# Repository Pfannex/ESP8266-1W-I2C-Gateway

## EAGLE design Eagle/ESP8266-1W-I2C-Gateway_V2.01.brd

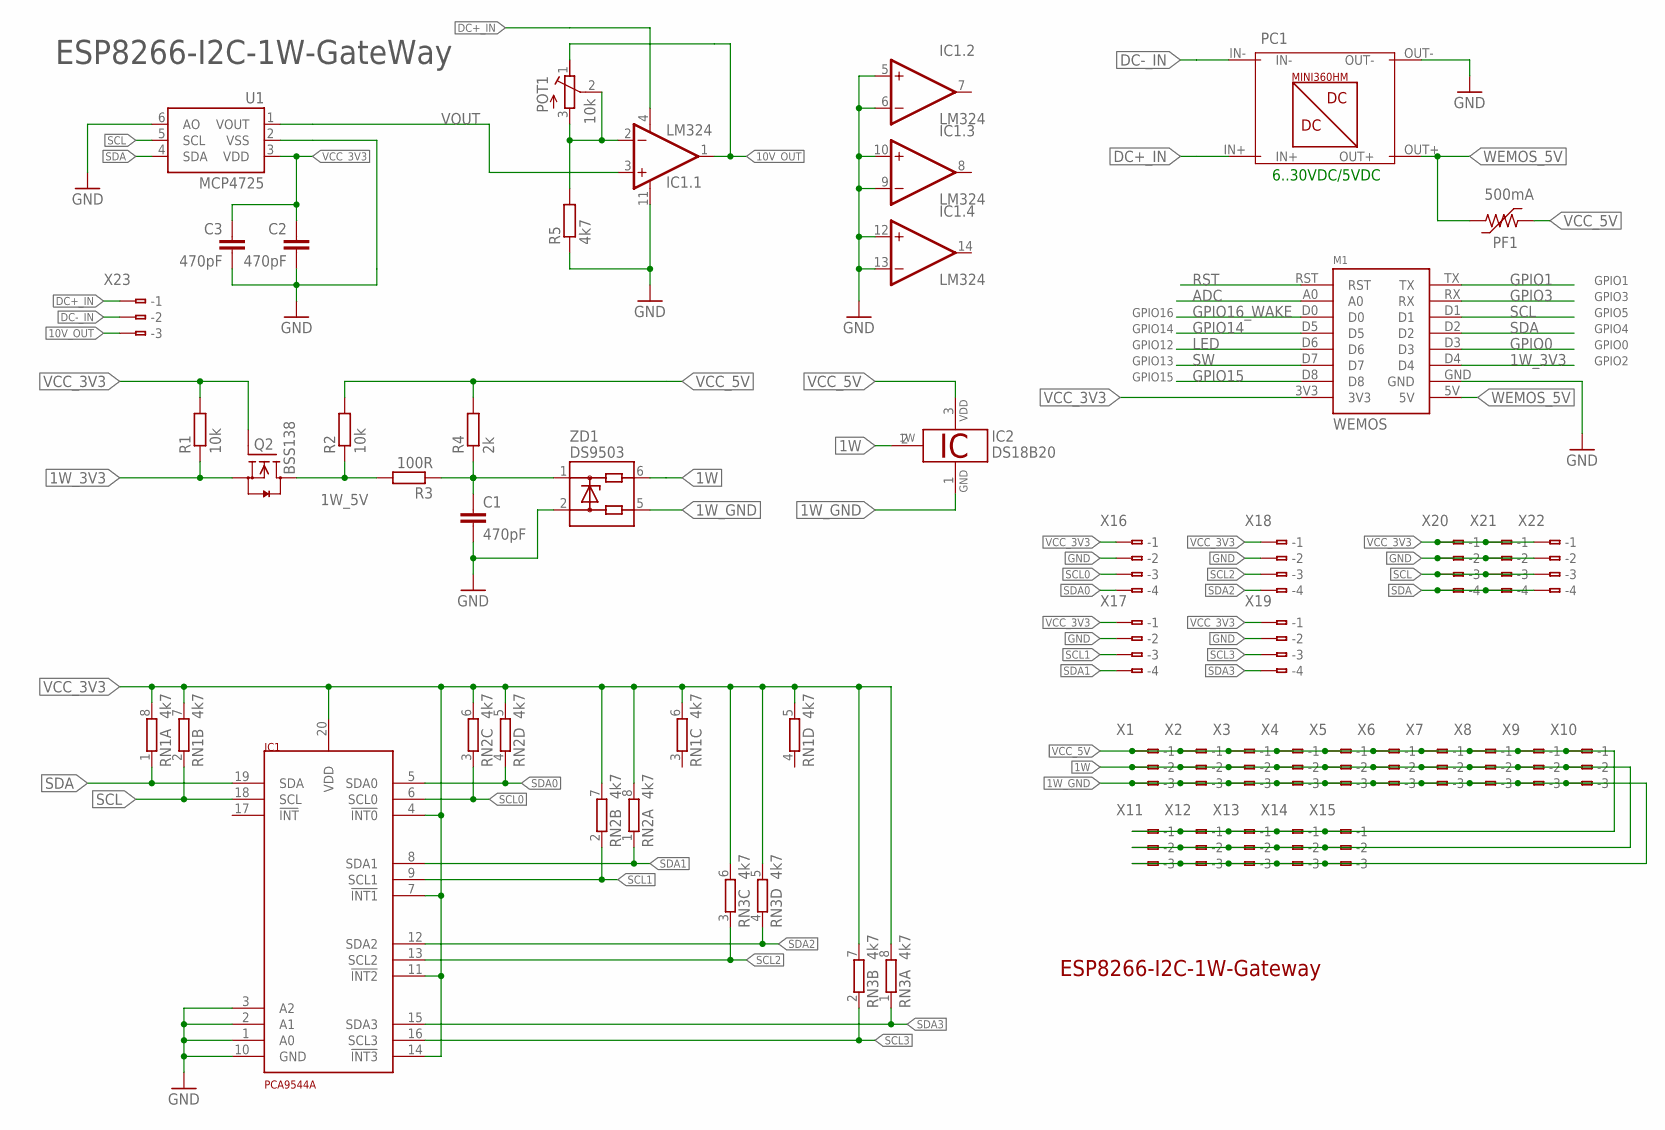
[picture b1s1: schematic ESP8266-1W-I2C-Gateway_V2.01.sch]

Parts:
C1, C2, C3: 470pF; C0805
IC1: PCA9544A; TSSOP20
IC1.: LM324; 2QSP14
IC2: DS18B20; TO92-
M1: WEMOS
PC1: MINI360HMTHROUGH-HOLE; MINI360HM
PF1: 500mA; F1206
POT1: 10k; BOURN_SMD_POTENTIOMETER
Q2: BSS138; SOT23
R1, R2: 10k; R0805
R3: 100R; R0805
R4: 2k; R0805
R5: 4k7; R0805
RN1, RN2, RN3: 4k7; 0603-ARC
U1: MCP4725; SOT23-6
X1, X2, X3, X4, X5, X6, X7, X8, X9, X10, X11, X12, X13, X14, X15, X23: MINI_3X
X16, X17, X18, X19, X20, X21, X22: MINI_4X
ZD1: DS9503; TSOC6_BYPASS_J

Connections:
1W: IC2.2 (1W), X1.B-2 (-2), X2.B-2 (-2), X3.B-2 (-2), X4.B-2 (-2), X5.B-2 (-2), X6.B-2 (-2), X7.B-2 (-2), X8.B-2 (-2), X9.B-2 (-2), X10.B-2 (-2), X11.B-2 (-2), X12.B-2 (-2), X13.B-2 (-2), X14.B-2 (-2), X15.B-2 (-2), ZD1.6
1W_3V3: M1.D4, Q2.2 (S), R1.1
1W_5V: Q2.3 (D), R2.1, R3.2
1W_GND: IC2.1 (GND), X1.B-3 (-3), X2.B-3 (-3), X3.B-3 (-3), X4.B-3 (-3), X5.B-3 (-3), X6.B-3 (-3), X7.B-3 (-3), X8.B-3 (-3), X9.B-3 (-3), X10.B-3 (-3), X11.B-3 (-3), X12.B-3 (-3), X13.B-3 (-3), X14.B-3 (-3), X15.B-3 (-3), ZD1.5
10V_OUT: IC1..1 (OUT), POT1.1 (A), X23.B-3 (-3)
ADC: M1.A0
DC+_IN: IC1..4 (V+), PC1.IN+, X23.B-1 (-1)
DC-_IN: PC1.IN-, X23.B-2 (-2)
GND: C1.2, C2.2, C3.2, IC1.1 (A0), IC1.2 (A1), IC1.3 (A2), IC1.10 (GND), IC1..5 (+IN), IC1..6 (-IN), IC1..9 (-IN), IC1..10 (+IN), IC1..11 (V-), IC1..12 (+IN), IC1..13 (-IN), M1.GND, PC1.OUT-, R5.1, U1.2 (VSS), U1.6 (AO), X16.B-2 (-2), X17.B-2 (-2), X18.B-2 (-2), X19.B-2 (-2), X20.B-2 (-2), X21.B-2 (-2), X22.B-2 (-2), ZD1.2
GPIO0: M1.D3
GPIO1: M1.TX
GPIO3: M1.RX
GPIO14: M1.D5
GPIO15: M1.D8
GPIO16_WAKE: M1.D0
LED: M1.D6
unnamed: IC1..2 (-IN), POT1.2 (S), POT1.3 (E), R5.2
unnamed: C1.1, R3.1, R4.1, ZD1.1
RST: M1.RST
SCL: IC1.18 (SCL), M1.D1, RN1.2 (1), U1.5 (SCL), X20.B-3 (-3), X21.B-3 (-3), X22.B-3 (-3)
SCL0: IC1.6 (SCL0), RN2.3 (1), X16.B-3 (-3)
SCL1: IC1.9 (SCL1), RN2.2 (1), X17.B-3 (-3)
SCL2: IC1.13 (SCL2), RN3.3 (1), X18.B-3 (-3)
SCL3: IC1.16 (SCL3), RN3.2 (1), X19.B-3 (-3)
SDA: IC1.19 (SDA), M1.D2, RN1.1, U1.4 (SDA), X20.B-4 (-4), X21.B-4 (-4), X22.B-4 (-4)
SDA0: IC1.5 (SDA0), RN2.4 (1), X16.B-4 (-4)
SDA1: IC1.8 (SDA1), RN2.1, X17.B-4 (-4)
SDA2: IC1.12 (SDA2), RN3.4 (1), X18.B-4 (-4)
SDA3: IC1.15 (SDA3), RN3.1, X19.B-4 (-4)
SW: M1.D7
VCC_3V3: C2.1, C3.1, IC1.4 (!INT0), IC1.7 (!INT1), IC1.11 (!INT2), IC1.14 (!INT3), IC1.20 (VDD), M1.3V3, Q2.1 (G), R1.2, RN1.5 (2), RN1.6 (2), RN1.7 (2), RN1.8 (2), RN2.5 (2), RN2.6 (2), RN2.7 (2), RN2.8 (2), RN3.5 (2), RN3.6 (2), RN3.7 (2), RN3.8 (2), U1.3 (VDD), X16.B-1 (-1), X17.B-1 (-1), X18.B-1 (-1), X19.B-1 (-1), X20.B-1 (-1), X21.B-1 (-1), X22.B-1 (-1)
VCC_5V: IC2.3 (VDD), PF1.1, R2.2, R4.2, X1.B-1 (-1), X2.B-1 (-1), X3.B-1 (-1), X4.B-1 (-1), X5.B-1 (-1), X6.B-1 (-1), X7.B-1 (-1), X8.B-1 (-1), X9.B-1 (-1), X10.B-1 (-1), X11.B-1 (-1), X12.B-1 (-1), X13.B-1 (-1), X14.B-1 (-1), X15.B-1 (-1)
VOUT: IC1..3 (+IN), U1.1 (VOUT)
WEMOS_5V: M1.5V, PC1.OUT+, PF1.2

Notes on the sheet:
ESP8266-I2C-1W-Gateway
ESP8266-I2C-1W-GateWay
GPIO16
GPIO5
GPIO4
GPIO0
GPIO2
GPIO14
GPIO12
GPIO13
GPIO15
GPIO3
GPIO1
6..30VDC/5VDC

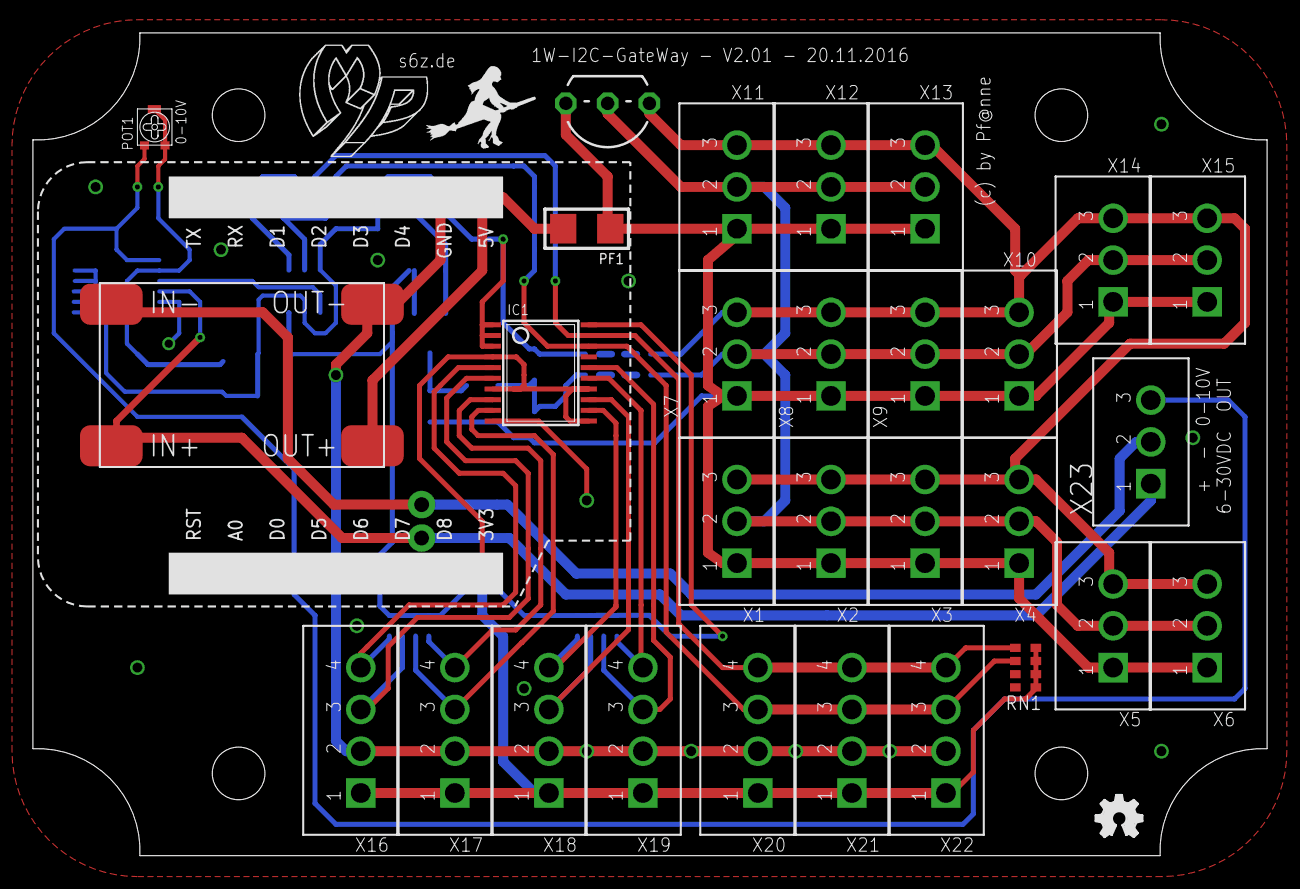
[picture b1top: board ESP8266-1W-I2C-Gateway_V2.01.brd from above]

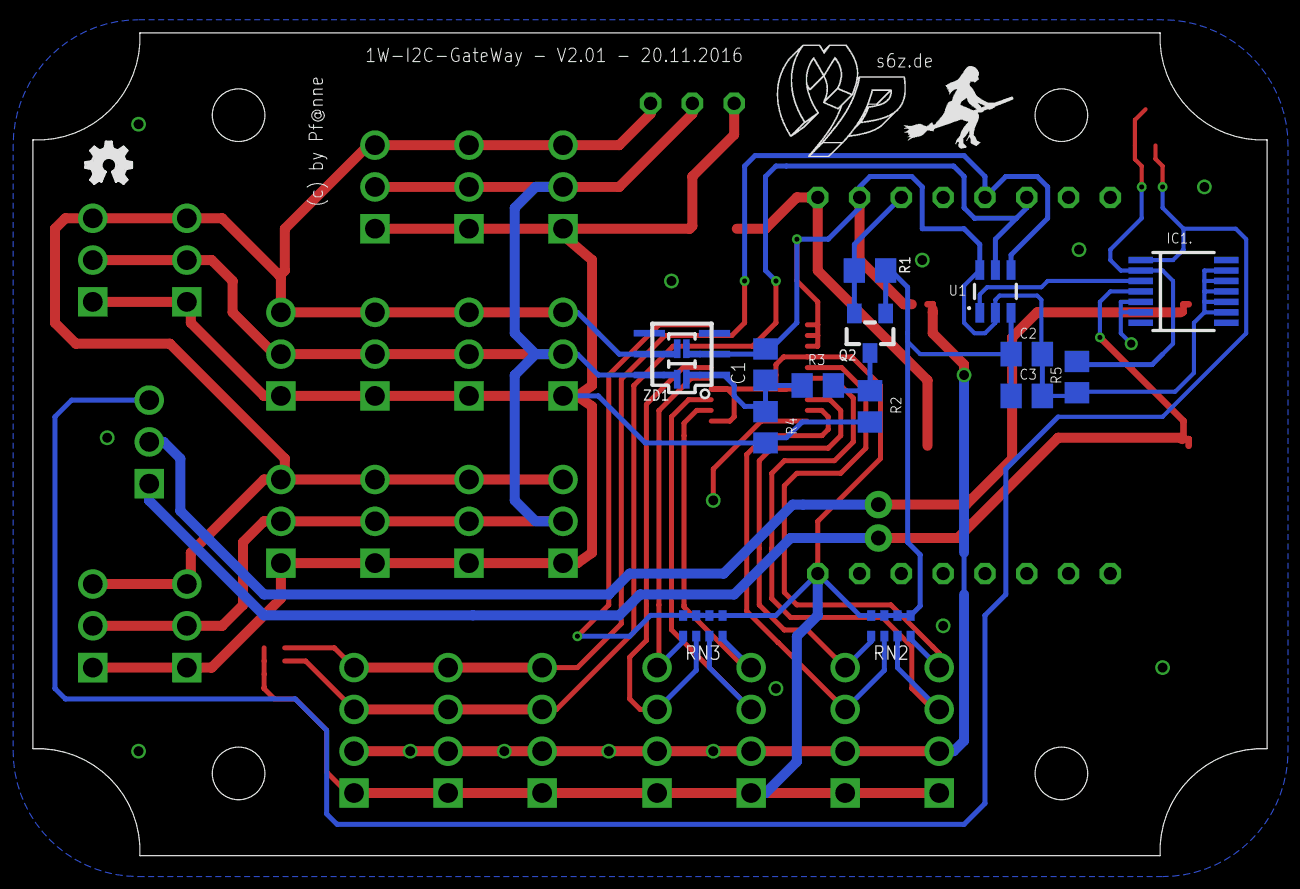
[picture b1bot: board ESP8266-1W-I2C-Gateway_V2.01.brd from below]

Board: 2 copper layers, 75.0 x 50.0 mm, 46 parts (15 on the bottom side), 24 nets.

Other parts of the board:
U$1, U$2: OSHW_FILLX100_NOTEXT

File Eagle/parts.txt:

Partlist

Exported from ESP8266-1W-I2C-Gateway_V2.00.sch at 13.11.2016 08:01

EAGLE Version 7.7.0 Copyright (c) 1988-2016 CadSoft

Assembly variant: 

Part     Value                 Device                                  Package                 Library                     Sheet

C1       470pF                 C-EUC0805                               C0805                   resistor                    1
C2       470pF                 C-EUC0805                               C0805                   resistor                    1
C3       470pF                 C-EUC0805                               C0805                   resistor                    1
IC1      PCA9544A              PCA9544A                                TSSOP20                 DSSCircuits                 1
IC1.     LM324                 LM324                                   2QSP14                  seanvoisen                  1
IC2      DS18B20               DS18B20                                 TO92-                   my                          1
M1       WEMOS                 WEMOS                                   WEMOS                   1455413453956-wemos         1
PC1      MINI360HMTHROUGH-HOLE MINI360HMTHROUGH-HOLE                   MINI360HM               ESP8266_1wire_Gateway_V1.15 1
PF1      500mA                 PTC-F1206                               F1206                   polyswitch                  1
POT1     10k                   BOURN_SMD_POTENTIOMETER2.1X2.7MMPACKAGE BOURN_SMD_POTENTIOMETER bourn_smd_potentiometers    1
Q2       BSS138                BSS138                                  SOT23                   my                          1
R1       10k                   R-EU_R0805                              R0805                   rcl                         1
R2       10k                   R-EU_R0805                              R0805                   rcl                         1
R3       100R                  R-EU_R0805                              R0805                   rcl                         1
R4       2k                    R-EU_R0805                              R0805                   rcl                         1
R5       4k7                   R-EU_R0805                              R0805                   rcl                         1
RN1      4k7                   4R-N0603-ARC                            0603-ARC                resistor-dil                1
RN2      4k7                   4R-N0603-ARC                            0603-ARC                resistor-dil                1
RN3      4k7                   4R-N0603-ARC                            0603-ARC                resistor-dil                1
U1       MCP4725               MCP4725SOT-23                           SOT23-6                 SparkFun-AnalogIC           1
X1                             MINI_3X                                 MINI_3X                 Terminal-2 - 3,5x5          1
X2                             MINI_3X                                 MINI_3X                 Terminal-2 - 3,5x5          1
X3                             MINI_3X                                 MINI_3X                 Terminal-2 - 3,5x5          1
X4                             MINI_3X                                 MINI_3X                 Terminal-2 - 3,5x5          1
X5                             MINI_3X                                 MINI_3X                 Terminal-2 - 3,5x5          1
X6                             MINI_3X                                 MINI_3X                 Terminal-2 - 3,5x5          1
X7                             MINI_3X                                 MINI_3X                 Terminal-2 - 3,5x5          1
X8                             MINI_3X                                 MINI_3X                 Terminal-2 - 3,5x5          1
X9                             MINI_3X                                 MINI_3X                 Terminal-2 - 3,5x5          1
X10                            MINI_3X                                 MINI_3X                 Terminal-2 - 3,5x5          1
X11                            MINI_3X                                 MINI_3X                 Terminal-2 - 3,5x5          1
X12                            MINI_3X                                 MINI_3X                 Terminal-2 - 3,5x5          1
X13                            MINI_3X                                 MINI_3X                 Terminal-2 - 3,5x5          1
X14                            MINI_3X                                 MINI_3X                 Terminal-2 - 3,5x5          1
X15                            MINI_3X                                 MINI_3X                 Terminal-2 - 3,5x5          1
X16                            MINI_4X                                 MINI_4X                 Terminal-2 - 3,5x5          1
X17                            MINI_4X                                 MINI_4X                 Terminal-2 - 3,5x5          1
X18                            MINI_4X                                 MINI_4X                 Terminal-2 - 3,5x5          1
X19                            MINI_4X                                 MINI_4X                 Terminal-2 - 3,5x5          1
X20                            MINI_4X                                 MINI_4X                 Terminal-2 - 3,5x5          1
X21                            MINI_4X                                 MINI_4X                 Terminal-2 - 3,5x5          1
X22                            MINI_4X                                 MINI_4X                 Terminal-2 - 3,5x5          1
X23                            MINI_3X                                 MINI_3X                 Terminal-2 - 3,5x5          1
ZD1      DS9503                DS9503_BYPASS_JP                        TSOC6_BYPASS_J          my                          1

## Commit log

2016-11-13 :lollipop: Added .gitattributes & .gitignore files
2016-11-13 Upload
2016-11-13 Upload Eagle
2016-11-17 Upload alphaV0.300
2016-11-17 BMP180 & HTU21 Plug&Play
2016-11-20 Upload alpha V0.311
2016-11-20 Upload Eagle V2.01
2016-12-13 commend out MySQL

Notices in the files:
parts and their libraries:
polyswitch: Copyright (C) 2008, Bob Starr
SparkFun-AnalogIC: Licensing:Creative Commons ShareAlike 4.0 International - https://creativecommons.org/licenses/by-sa/4.0
